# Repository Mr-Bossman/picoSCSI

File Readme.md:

# PicoSCSI

## A SD sard to Parallel SCSI hard drive emulator

### Board

The board design is lossely based on the [BlueSCSI V1](https://github.com/erichelgeson/BlueSCSI) and the [ZuluSCSI Pico](https://github.com/ZuluSCSI/ZuluSCSI-Pico-OSHW).
The [RP2350](https://www.raspberrypi.com/products/rp2350/) the MCU on the [Raspberry PI Pico 2](https://www.raspberrypi.com/products/raspberry-pi-pico-2/) is [5V tollerant](https://www.raspberrypi.com/news/rp2350-a4-rp2354-and-a-new-hacking-challenge/) meaning no level translation logic is nessasary.
Like BlueSCSI this outputs 3.3V to the bus, which is compliant with LV SCSI.

#### Documents relating to 5V tollerance
[Piers Finlayson's video](https://www.youtube.com/watch?v=Zy8IMe6fMI4&t=1768s) on the RP2350 variant of
[one-rom](https://github.com/piersfinlayson/one-rom/blob/main/sdrr-pcb/verified/rp2350-24-pin-rev-a/one-rom-24-pin-rp2350-rev-a-schematic.pdf) talks about caveats this may have.
The A4 silicon revision adds support for this https://www.raspberrypi.com/news/rp2350-a4-rp2354-and-a-new-hacking-challenge noted at the bottom.

### Firmware

Coming soon will be based on [ZuluSCSI firmware](https://github.com/ZuluSCSI/ZuluSCSI-firmware)

### TODO:

Add both SMD and THT versions
Add DB25 version
Fix Pi Pico not having combined THT and SMD footprint

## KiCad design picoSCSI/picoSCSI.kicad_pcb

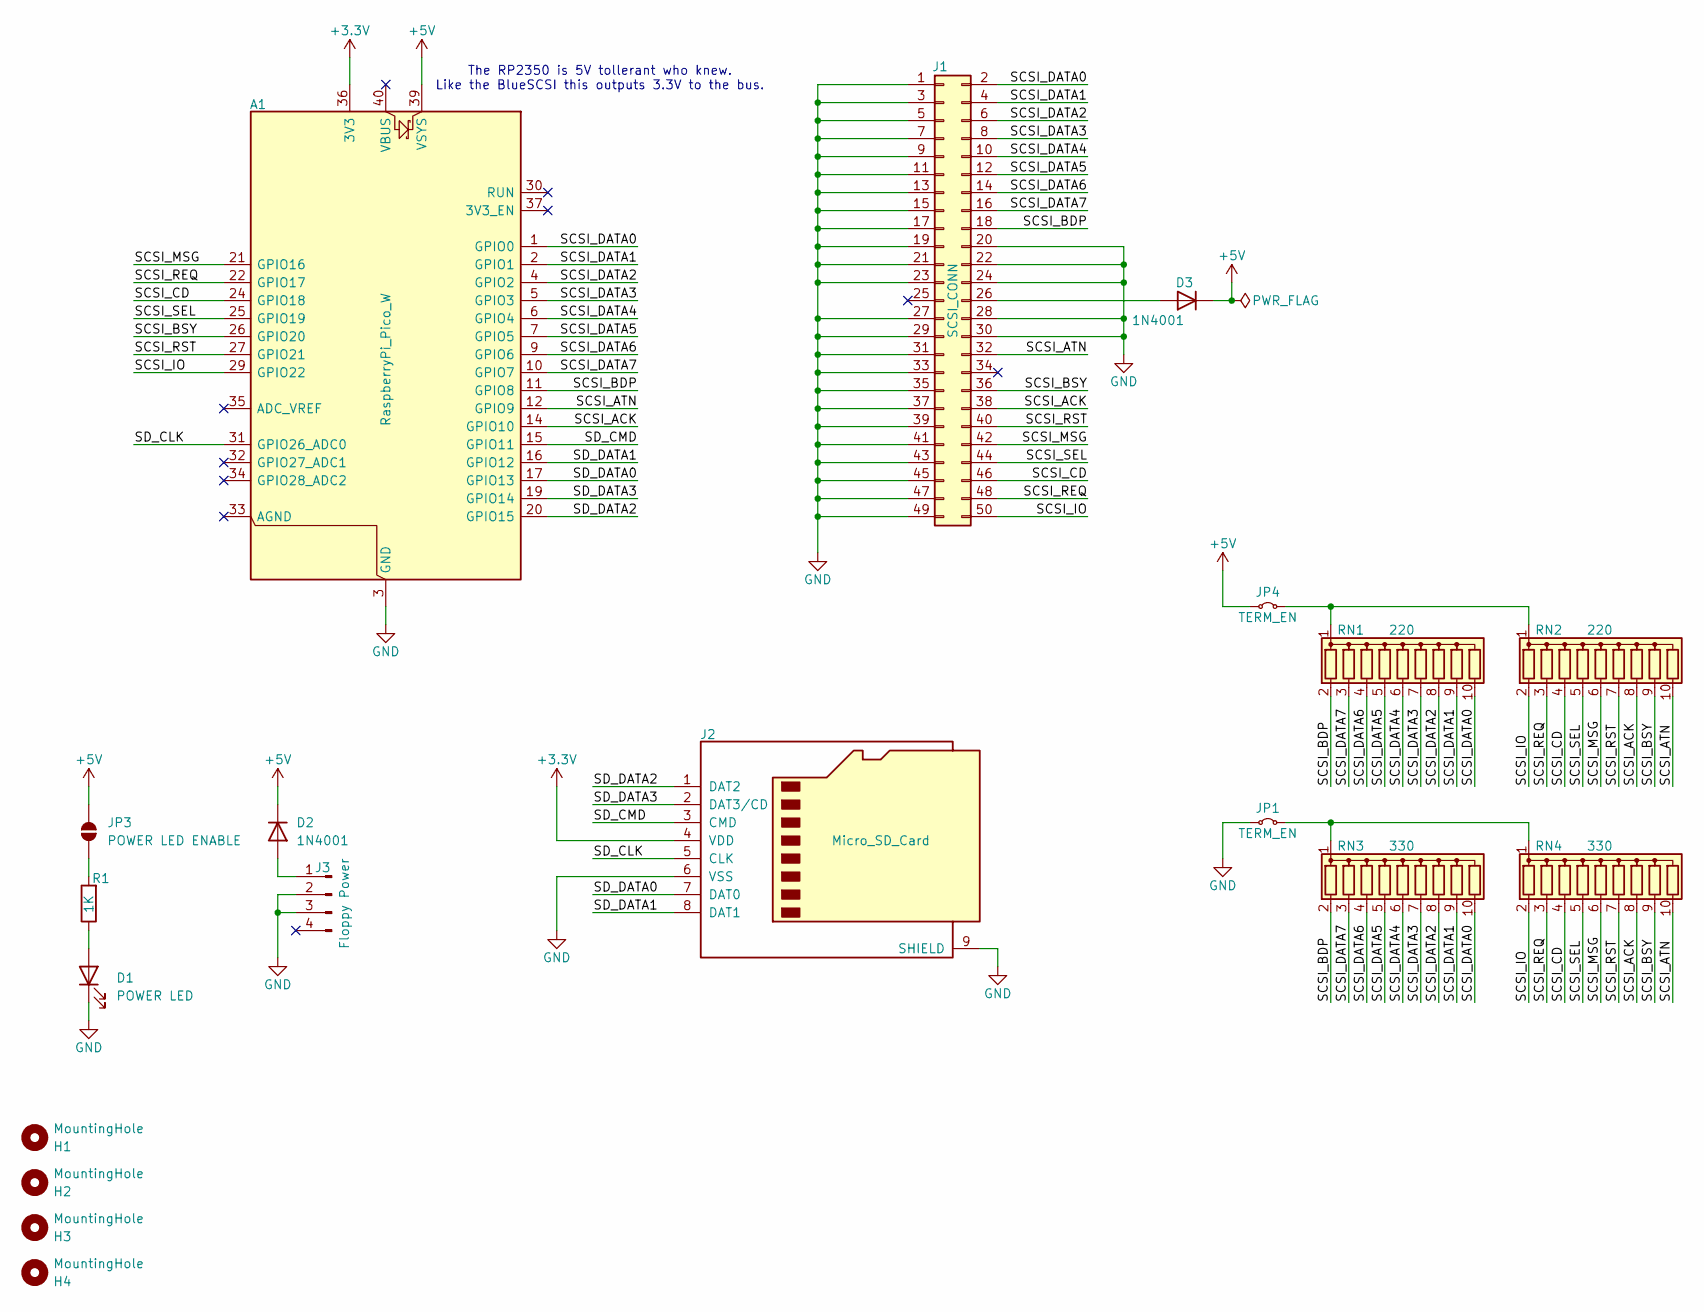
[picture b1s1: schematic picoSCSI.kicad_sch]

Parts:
A1: RaspberryPi_Pico_W; RaspberryPi_Pico_W_SMD_HandSolder
D1: POWER LED; LED_D5.0mm
D2, D3: 1N4001; D_DO-41_SOD81_P7.62mm_Horizontal
H1, H2, H3, H4: MountingHole; MountingHole_3.2mm_M3_ISO7380
J1: SCSI_CONN; IDC-Header_2x25_P2.54mm_Vertical
J2: Micro_SD_Card; microSD_HC_Wuerth_693072010801
J3: Floppy Power; JST_PH_B4B-PH-K_1x04_P2.00mm_Vertical
JP1, JP4: TERM_EN; PinSocket_1x02_P2.54mm_Vertical
JP3: POWER LED ENABLE; SolderJumper-2_P1.3mm_Open_RoundedPad1.0x1.5mm
R1: 1K; R_Axial_DIN0204_L3.6mm_D1.6mm_P5.08mm_Horizontal
RN1, RN2: 220; R_Array_SIP10
RN3, RN4: 330; R_Array_SIP10

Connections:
+3.3V: A1.36 (3V3), J2.4 (VDD)
+5V: A1.39 (VSYS), D2.1 (K), D3.1 (K), JP3.2 (B), JP4.1 (A)
/SCSI_ACK: A1.14 (GPIO10), J1.38, RN2.8 (R7), RN4.8 (R7)
/SCSI_ATN: A1.12 (GPIO9), J1.32, RN2.10 (R9), RN4.10 (R9)
/SCSI_BDP: A1.11 (GPIO8), J1.18, RN1.2 (R1), RN3.2 (R1)
/SCSI_BSY: A1.26 (GPIO20), J1.36, RN2.9 (R8), RN4.9 (R8)
/SCSI_CD: A1.24 (GPIO18), J1.46, RN2.4 (R3), RN4.4 (R3)
/SCSI_DATA0: A1.1 (GPIO0), J1.2, RN1.10 (R9), RN3.10 (R9)
/SCSI_DATA1: A1.2 (GPIO1), J1.4, RN1.9 (R8), RN3.9 (R8)
/SCSI_DATA2: A1.4 (GPIO2), J1.6, RN1.8 (R7), RN3.8 (R7)
/SCSI_DATA3: A1.5 (GPIO3), J1.8, RN1.7 (R6), RN3.7 (R6)
/SCSI_DATA4: A1.6 (GPIO4), J1.10, RN1.6 (R5), RN3.6 (R5)
/SCSI_DATA5: A1.7 (GPIO5), J1.12, RN1.5 (R4), RN3.5 (R4)
/SCSI_DATA6: A1.9 (GPIO6), J1.14, RN1.4 (R3), RN3.4 (R3)
/SCSI_DATA7: A1.10 (GPIO7), J1.16, RN1.3 (R2), RN3.3 (R2)
/SCSI_IO: A1.29 (GPIO22), J1.50, RN2.2 (R1), RN4.2 (R1)
/SCSI_MSG: A1.21 (GPIO16), J1.42, RN2.6 (R5), RN4.6 (R5)
/SCSI_REQ: A1.22 (GPIO17), J1.48, RN2.3 (R2), RN4.3 (R2)
/SCSI_RST: A1.27 (GPIO21), J1.40, RN2.7 (R6), RN4.7 (R6)
/SCSI_SEL: A1.25 (GPIO19), J1.44, RN2.5 (R4), RN4.5 (R4)
/SD_CLK: A1.31 (GPIO26_ADC0), J2.5 (CLK)
/SD_CMD: A1.15 (GPIO11), J2.3 (CMD)
/SD_DATA0: A1.17 (GPIO13), J2.7 (DAT0)
/SD_DATA1: A1.16 (GPIO12), J2.8 (DAT1)
/SD_DATA2: A1.20 (GPIO15), J2.1 (DAT2)
/SD_DATA3: A1.19 (GPIO14), J2.2 (DAT3/CD)
GND: A1.3 (GND), A1.8 (GND), A1.13 (GND), A1.18 (GND), A1.23 (GND), A1.28 (GND), A1.38 (GND), D1.1 (K), J1.1, J1.3, J1.5, J1.7, J1.9, J1.11, J1.13, J1.15, J1.17, J1.19, J1.20, J1.21, J1.22, J1.23, J1.24, J1.27, J1.28, J1.29, J1.30, J1.31, J1.33, J1.35, J1.37, J1.39, J1.41, J1.43, J1.45, J1.47, J1.49, J2.6 (VSS), J2.9 (SHIELD), J3.2, J3.3, JP1.1 (A)
unnamed: D1.2 (A), R1.1
unnamed: D2.2 (A), J3.1
unnamed: D3.2 (A), J1.26
unnamed: JP1.2 (B), RN3.1 (common), RN4.1 (common)
unnamed: JP3.1 (A), R1.2
unnamed: JP4.2 (B), RN1.1 (common), RN2.1 (common)

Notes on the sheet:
The RP2350 is 5V tollerant who knew. Like the BlueSCSI this outputs 3.3V to the bus.

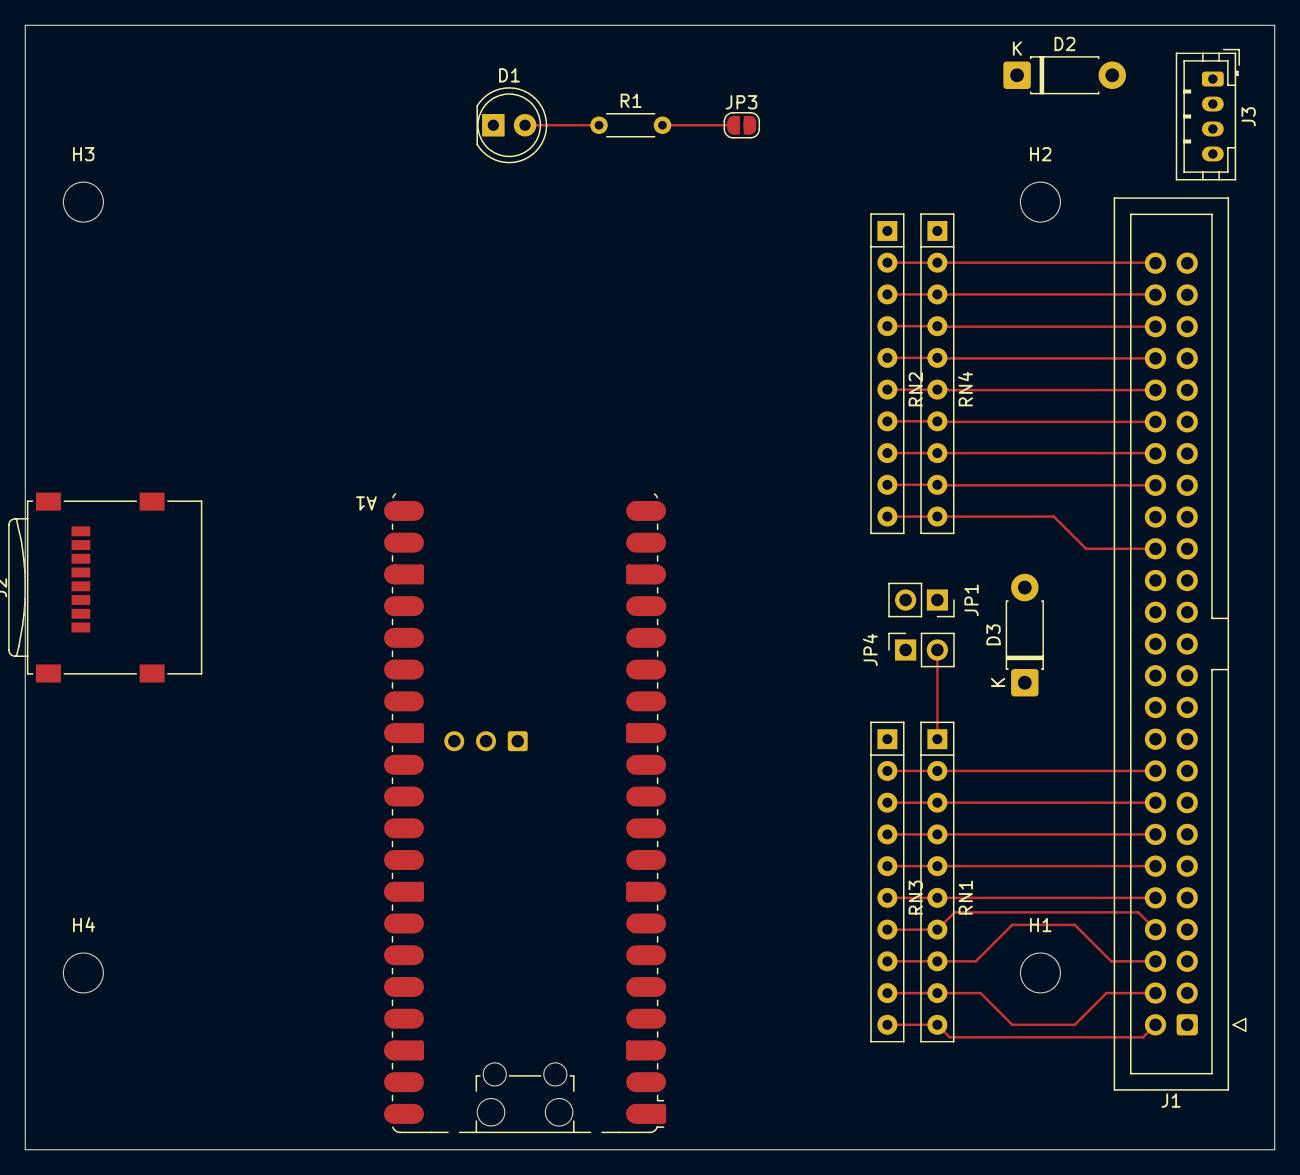
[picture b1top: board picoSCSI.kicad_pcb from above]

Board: 2 copper layers, 100.0 x 90.0 mm, 19 parts (0 on the bottom side), 33 nets.

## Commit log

2025-08-30 init
2025-08-30 Update readme with links and todo
2025-08-30 Start PCB
